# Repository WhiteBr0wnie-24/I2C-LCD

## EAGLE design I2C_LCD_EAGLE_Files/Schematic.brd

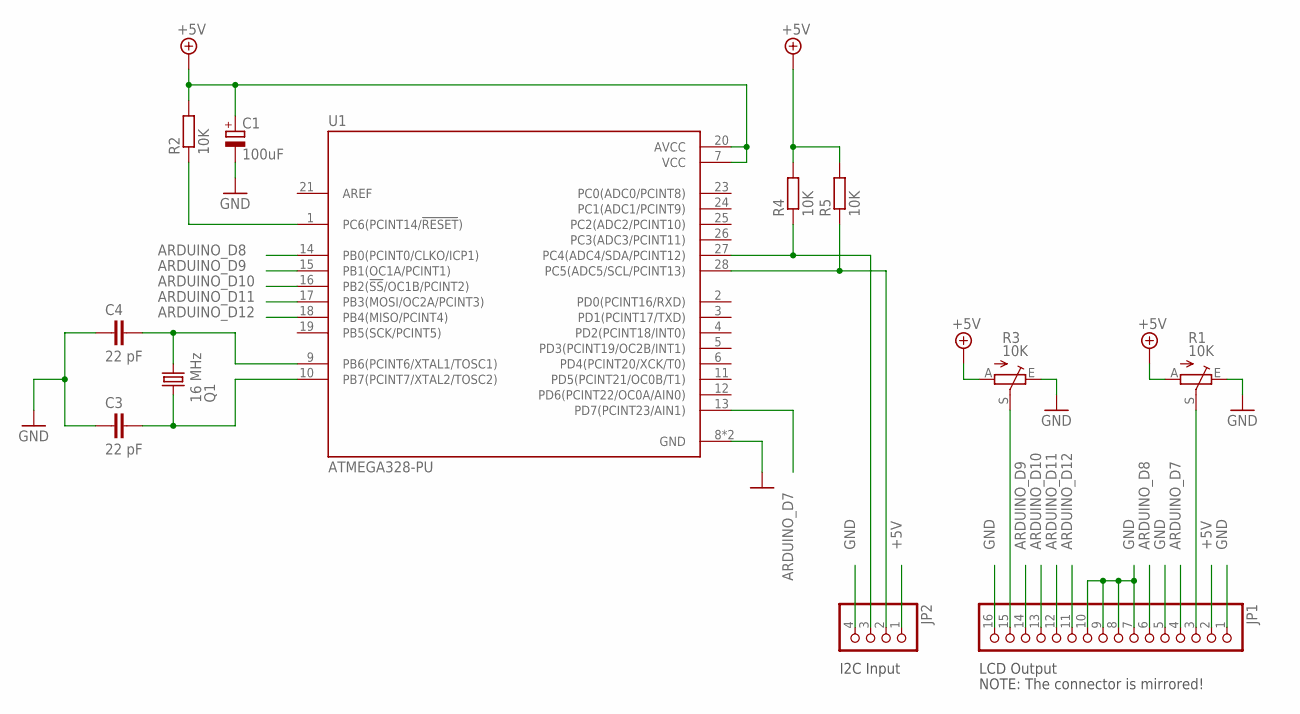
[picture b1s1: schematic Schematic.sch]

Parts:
C1: 100uF; E2,5-6E
C3, C4: 22 pF; C5B2.5
JP1: PINHD-1X16; 1X16
JP2: PINHD-1X4/90; 1X04/90
Q1: 16 MHz; HC49/S
R1, R3: 10K; B25P
R2, R4, R5: 10K; 0204/7
U1: ATMEGA328-PU; DIP787W46P254L3467H508Q28

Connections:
+5V: C1.+, JP1.2, JP2.1, R1.A, R2.2, R3.A, R4.2, R5.2, U1.7 (VCC), U1.20 (AVCC)
ARDUINO_D7: JP1.4, U1.13 (PD7(PCINT23/AIN1))
ARDUINO_D8: JP1.6, U1.14 (PB0(PCINT0/CLKO/ICP1))
ARDUINO_D9: JP1.14, U1.15 (PB1(OC1A/PCINT1))
ARDUINO_D10: JP1.13, U1.16 (PB2(!SS!/OC1B/PCINT2))
ARDUINO_D11: JP1.12, U1.17 (PB3(MOSI/OC2A/PCINT3))
ARDUINO_D12: JP1.11, U1.18 (PB4(MISO/PCINT4))
GND: C1.-, C3.1, C4.1, JP1.1, JP1.5, JP1.7, JP1.8, JP1.9, JP1.10, JP1.16, JP2.4, R1.E, R3.E, U1.8 (GND), U1.22 (GND)
unnamed: JP1.15, R3.S
unnamed: JP2.3, R4.1, U1.27 (PC4(ADC4/SDA/PCINT12))
unnamed: JP1.3, R1.S
unnamed: JP2.2, R5.1, U1.28 (PC5(ADC5/SCL/PCINT13))
unnamed: C4.2, Q1.2, U1.9 (PB6(PCINT6/XTAL1/TOSC1))
unnamed: C3.2, Q1.1, U1.10 (PB7(PCINT7/XTAL2/TOSC2))
unnamed: R2.1, U1.1 (PC6(PCINT14/!RESET!))

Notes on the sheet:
LCD Output
I2C Input
NOTE: The connector is mirrored!

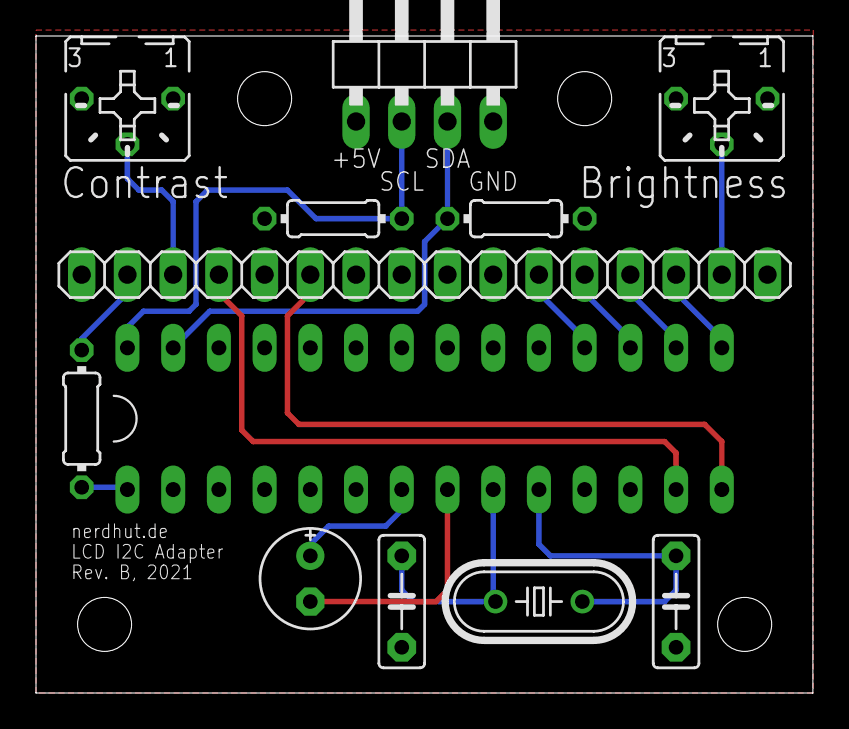
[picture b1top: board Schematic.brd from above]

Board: 2 copper layers, 43.2 x 36.5 mm, 12 parts (0 on the bottom side), 15 nets.

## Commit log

2021-10-24 Added gitignore
2021-10-24 Added comments
